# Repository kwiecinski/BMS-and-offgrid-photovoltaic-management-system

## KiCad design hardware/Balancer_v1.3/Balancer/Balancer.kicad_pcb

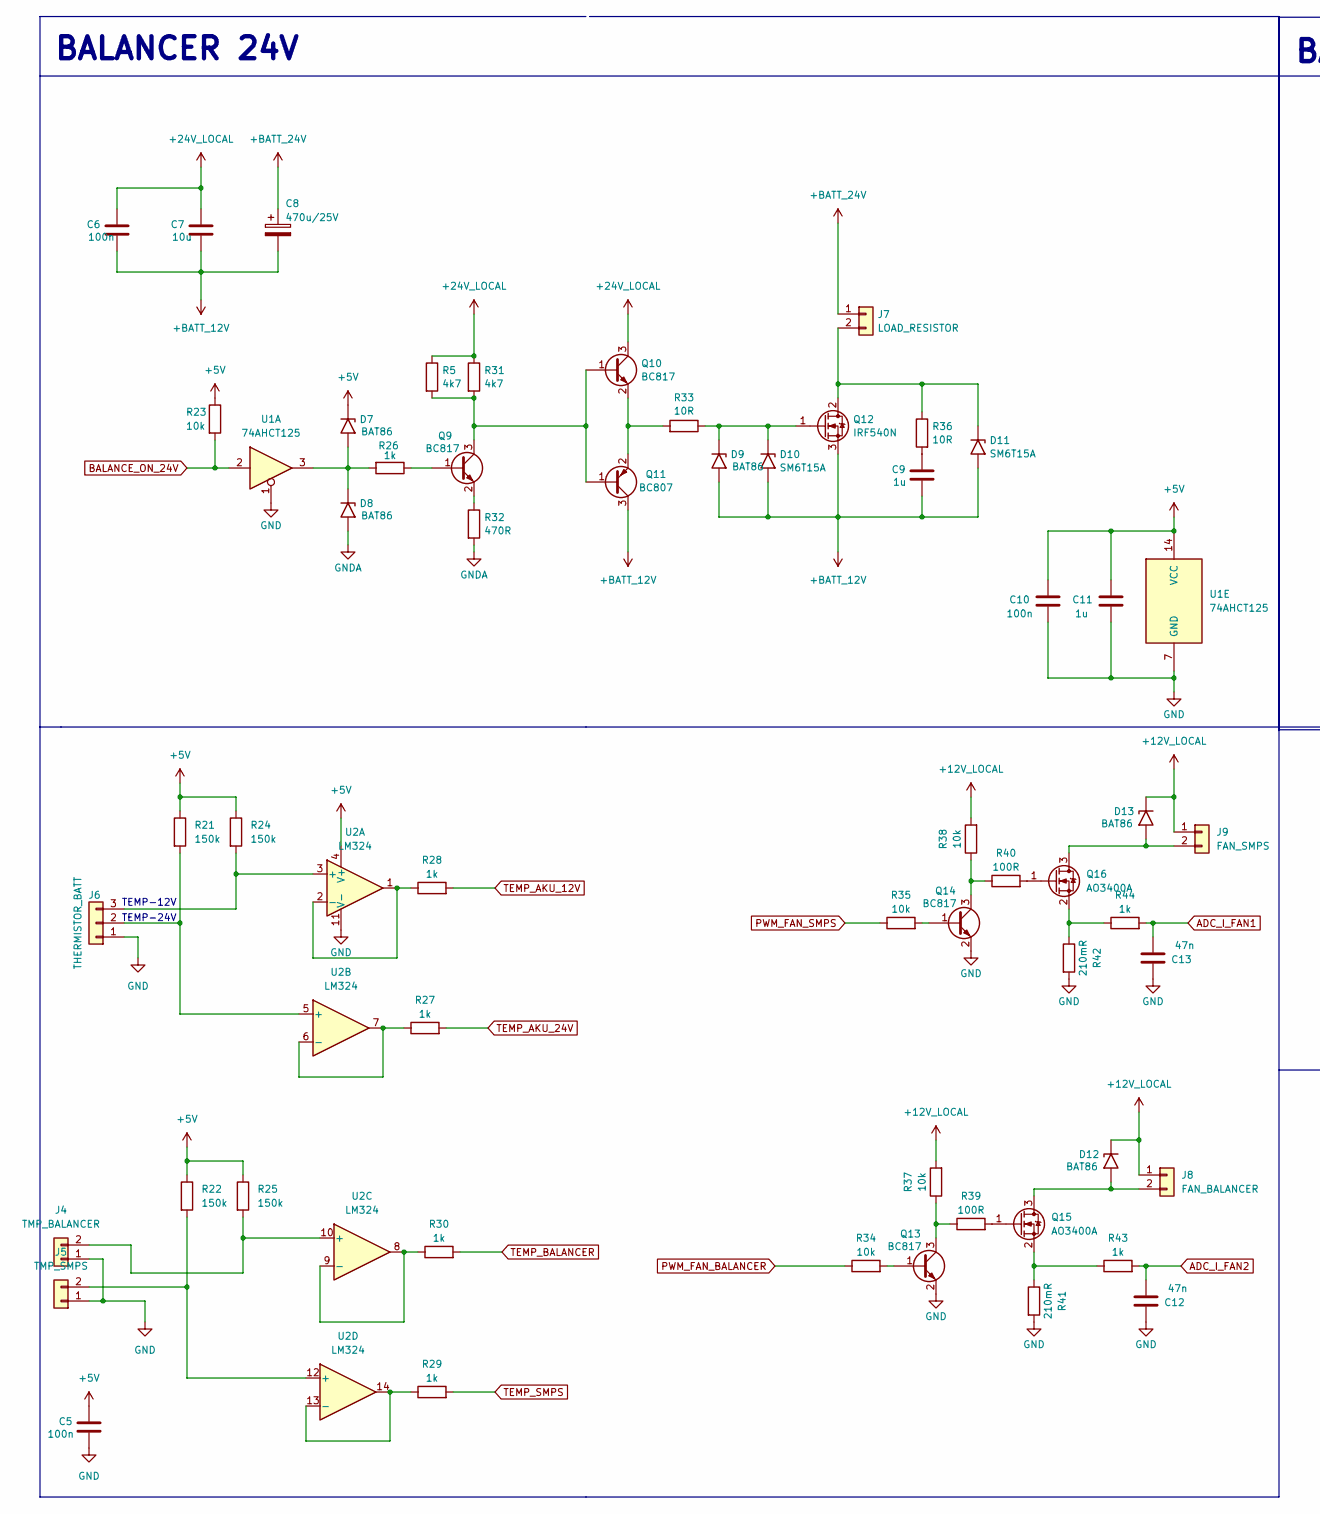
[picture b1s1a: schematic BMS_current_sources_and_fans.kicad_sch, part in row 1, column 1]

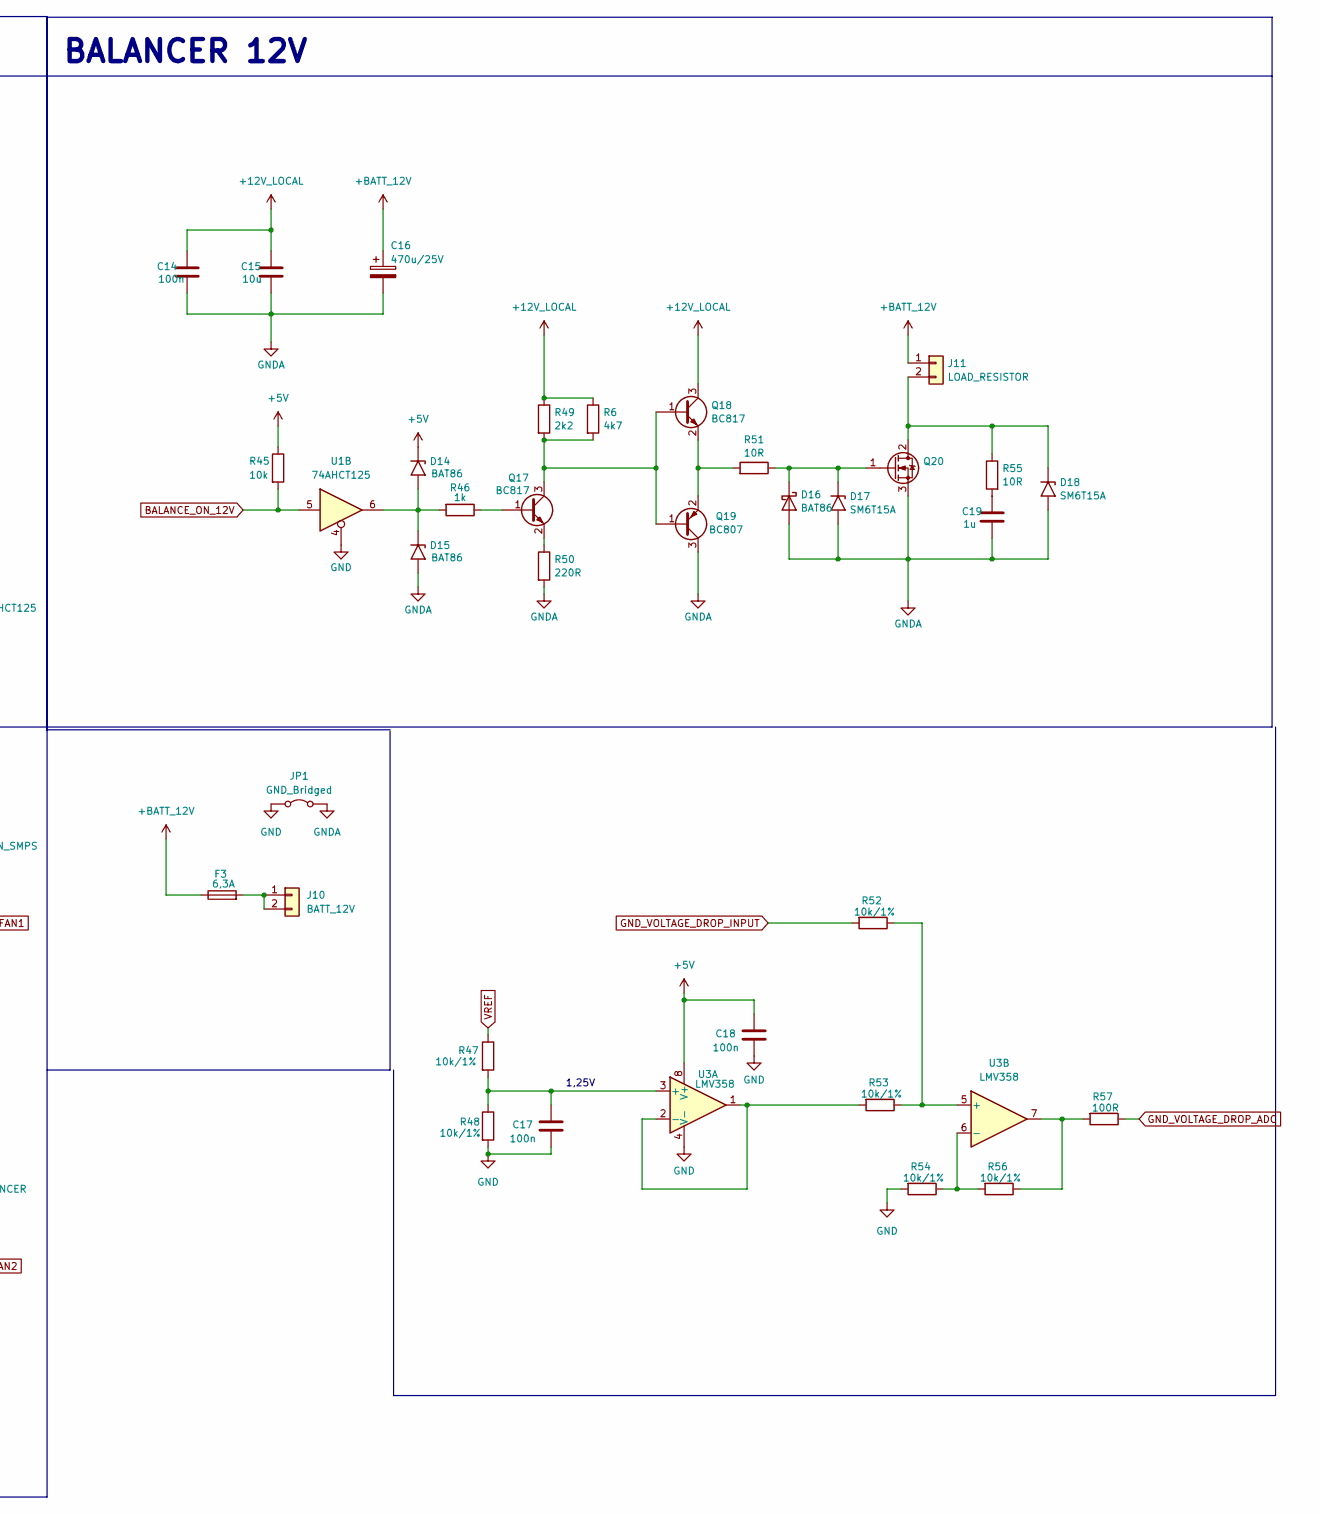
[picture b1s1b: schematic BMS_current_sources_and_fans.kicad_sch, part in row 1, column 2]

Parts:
C5, C6, C10, C14, C17, C18: 100n; C_0805_2012Metric_Pad1.18x1.45mm_HandSolder
C7, C15: 10u; C_0805_2012Metric_Pad1.18x1.45mm_HandSolder
C8, C16: 470u/25V; CP_Radial_D8.0mm_P2.50mm
C9, C19: 1u; C_Disc_D5.0mm_W2.5mm_P2.50mm
C11: 1u; C_0805_2012Metric_Pad1.18x1.45mm_HandSolder
C12, C13: 47n; C_0805_2012Metric_Pad1.18x1.45mm_HandSolder
D7, D8, D9, D12, D13, D14, D15, D16: BAT86; D_MiniMELF
D10, D11, D17, D18: SM6T15A; D_SMB
F3: 6,3A; Fuseholder_Clip-5x20mm_Eaton_1A5601-01_Inline_P20.80x6.76mm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
J4: TMP_BALANCER; JST_EH_B2B-EH-A_1x02_P2.50mm_Vertical
J5: TMP_SMPS; JST_EH_B2B-EH-A_1x02_P2.50mm_Vertical
J6: THERMISTOR_BATT; JST_EH_B3B-EH-A_1x03_P2.50mm_Vertical
J7, J11: LOAD_RESISTOR; Conn_1x2_wire
J8: FAN_BALANCER; JST_EH_B2B-EH-A_1x02_P2.50mm_Vertical
J9: FAN_SMPS; JST_EH_B2B-EH-A_1x02_P2.50mm_Vertical
J10: BATT_12V; Flat-6,3mm-connector-2P
JP1: GND_Bridged; SolderJumper-2_P1.3mm_Bridged2Bar_Pad1.0x1.5mm
Q9, Q10, Q13, Q14, Q17, Q18: BC817; SOT-23
Q11, Q19: BC807; SOT-23
Q12, Q20: IRF540N; TO-220-3_Vertical-little-bigger pads
Q15, Q16: AO3400A; SOT-23
R5, R6, R31: 4k7; R_1206_3216Metric_Pad1.30x1.75mm_HandSolder
R21, R22, R24, R25: 150k; R_0805_2012Metric_Pad1.20x1.40mm_HandSolder
R23, R34, R35, R37, R38, R45: 10k; R_0805_2012Metric_Pad1.20x1.40mm_HandSolder
R26, R27, R28, R29, R30, R43, R44, R46: 1k; R_0805_2012Metric_Pad1.20x1.40mm_HandSolder
R32: 470R; R_0805_2012Metric_Pad1.20x1.40mm_HandSolder
R33, R51: 10R; R_0805_2012Metric_Pad1.20x1.40mm_HandSolder
R36, R55: 10R; R_Axial_DIN0204_L3.6mm_D1.6mm_P7.62mm_Horizontal
R39, R40, R57: 100R; R_0805_2012Metric_Pad1.20x1.40mm_HandSolder
R41, R42: 210mR; R_0805_2012Metric_Pad1.20x1.40mm_HandSolder
R47, R48, R52, R53, R54, R56: 10k/1%; R_0805_2012Metric_Pad1.20x1.40mm_HandSolder
R49: 2k2; R_1206_3216Metric_Pad1.30x1.75mm_HandSolder
R50: 220R; R_0805_2012Metric_Pad1.20x1.40mm_HandSolder
U1: 74AHCT125; SOIC-14_3.9x8.7mm_P1.27mm
U2: LM324; SOIC-14_3.9x8.7mm_P1.27mm
U3: LMV358; SOIC-8_3.9x4.9mm_P1.27mm

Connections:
+5V: C5.1, C10.1, C11.1, C18.1, D7.1 (A1), D14.1 (A1), R21.1, R22.1, R23.1, R24.1, R25.1, R45.1, U1.14 (VCC), U2.4 (V+), U3.8 (V+); also elsewhere on the board
+12V_LOCAL: C14.1, C15.1, D12.1 (A1), D13.1 (A1), J8.1, J9.1, Q18.3 (C), R6.1, R37.2, R38.2, R49.1; also elsewhere on the board
+24V_LOCAL: C6.1, C7.1, Q10.3 (C), R5.1, R31.1; also elsewhere on the board
+BATT_12V: C6.2, C7.2, C8.2, C9.2, C16.1, D9.2 (A2), D10.2 (A2), D11.2 (A2), F3.1, J11.1, Q11.3 (C), Q12.3 (S); also elsewhere on the board
+BATT_24V: C8.1, J7.1; also elsewhere on the board
ADC_I_FAN1: C13.2, R44.2; also elsewhere on the board
ADC_I_FAN2: C12.2, R43.2; also elsewhere on the board
BALANCE_ON_12V: R45.2, U1.5; also elsewhere on the board
BALANCE_ON_24V: R23.2, U1.2; also elsewhere on the board
GND: C5.2, C10.2, C11.2, C12.1, C13.1, C17.2, C18.2, J4.1, J5.1, J6.1, JP1.1 (A), Q13.2 (E), Q14.2 (E), R41.2, R42.2, R48.2, R54.2, U1.1, U1.4, U1.7 (GND), U2.11 (V-), U3.4 (V-); also elsewhere on the board
GNDA: C14.2, C15.2, C16.2, C19.2, D8.2 (A2), D15.2 (A2), D16.2 (A), D17.2 (A2), D18.2 (A2), JP1.2 (B), Q19.3 (C), Q20.3 (S), R32.2, R50.2; also elsewhere on the board
GND_VOLTAGE_DROP_ADC: R57.1; also elsewhere on the board
GND_VOLTAGE_DROP_INPUT: R52.2; also elsewhere on the board
unnamed: C9.1, R36.2
unnamed: C19.1, R55.2
unnamed: D7.2 (A2), D8.1 (A1), R26.2, U1.3
unnamed: D9.1 (A1), D10.1 (A1), Q12.1 (G), R33.1
unnamed: D11.1 (A1), J7.2, Q12.2 (D), R36.1
unnamed: D12.2 (A2), J8.2, Q15.3 (D)
unnamed: D13.2 (A2), J9.2, Q16.3 (D)
unnamed: D14.2 (A2), D15.1 (A1), R46.2, U1.6
unnamed: D16.1 (K), D17.1 (A1), Q20.1 (G), R51.1
unnamed: D18.1 (A1), J11.2, Q20.2 (D), R55.1
unnamed: J4.2, R25.2, U2.10 (+)
unnamed: J5.2, R22.2, U2.12 (+)
unnamed: J6.2, R21.2, U2.5 (+)
unnamed: J6.3, R24.2, U2.3 (+)
unnamed: F3.2, J10.1, J10.2
unnamed: Q9.1 (B), R26.1
unnamed: Q9.2 (E), R32.1
unnamed: Q9.3 (C), Q10.1 (B), Q11.1 (B), R5.2, R31.2
unnamed: Q10.2 (E), Q11.2 (E), R33.2
unnamed: Q13.1 (B), R34.2
unnamed: Q13.3 (C), R37.1, R39.1
unnamed: Q14.1 (B), R35.2
unnamed: Q14.3 (C), R38.1, R40.1
unnamed: Q15.1 (G), R39.2
unnamed: Q15.2 (S), R41.1, R43.1
unnamed: Q16.1 (G), R40.2
unnamed: Q16.2 (S), R42.1, R44.1
unnamed: Q17.1 (B), R46.1
unnamed: Q17.3 (C), Q18.1 (B), Q19.1 (B), R6.2, R49.2
unnamed: Q17.2 (E), R50.1
unnamed: Q18.2 (E), Q19.2 (E), R51.2
unnamed: R56.1, R57.2, U3.7
unnamed: R28.1, U2.1, U2.2 (-)
unnamed: R27.1, U2.6 (-), U2.7
unnamed: R30.1, U2.8, U2.9 (-)
unnamed: R29.1, U2.13 (-), U2.14
unnamed: C17.1, R47.2, R48.1, U3.3 (+)
unnamed: R53.2, U3.1, U3.2 (-)
unnamed: R52.1, R53.1, U3.5 (+)
unnamed: R54.1, R56.2, U3.6 (-)
PWM_FAN_BALANCER: R34.1; also elsewhere on the board
PWM_FAN_SMPS: R35.1; also elsewhere on the board
TEMP_AKU_12V: R28.2; also elsewhere on the board
TEMP_AKU_24V: R27.2; also elsewhere on the board
TEMP_BALANCER: R30.2; also elsewhere on the board
TEMP_SMPS: R29.2; also elsewhere on the board
VREF: R47.1; also elsewhere on the board

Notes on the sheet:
1,25V
BALANCER 12V
TEMP-12V
TEMP-24V
BALANCER 24V

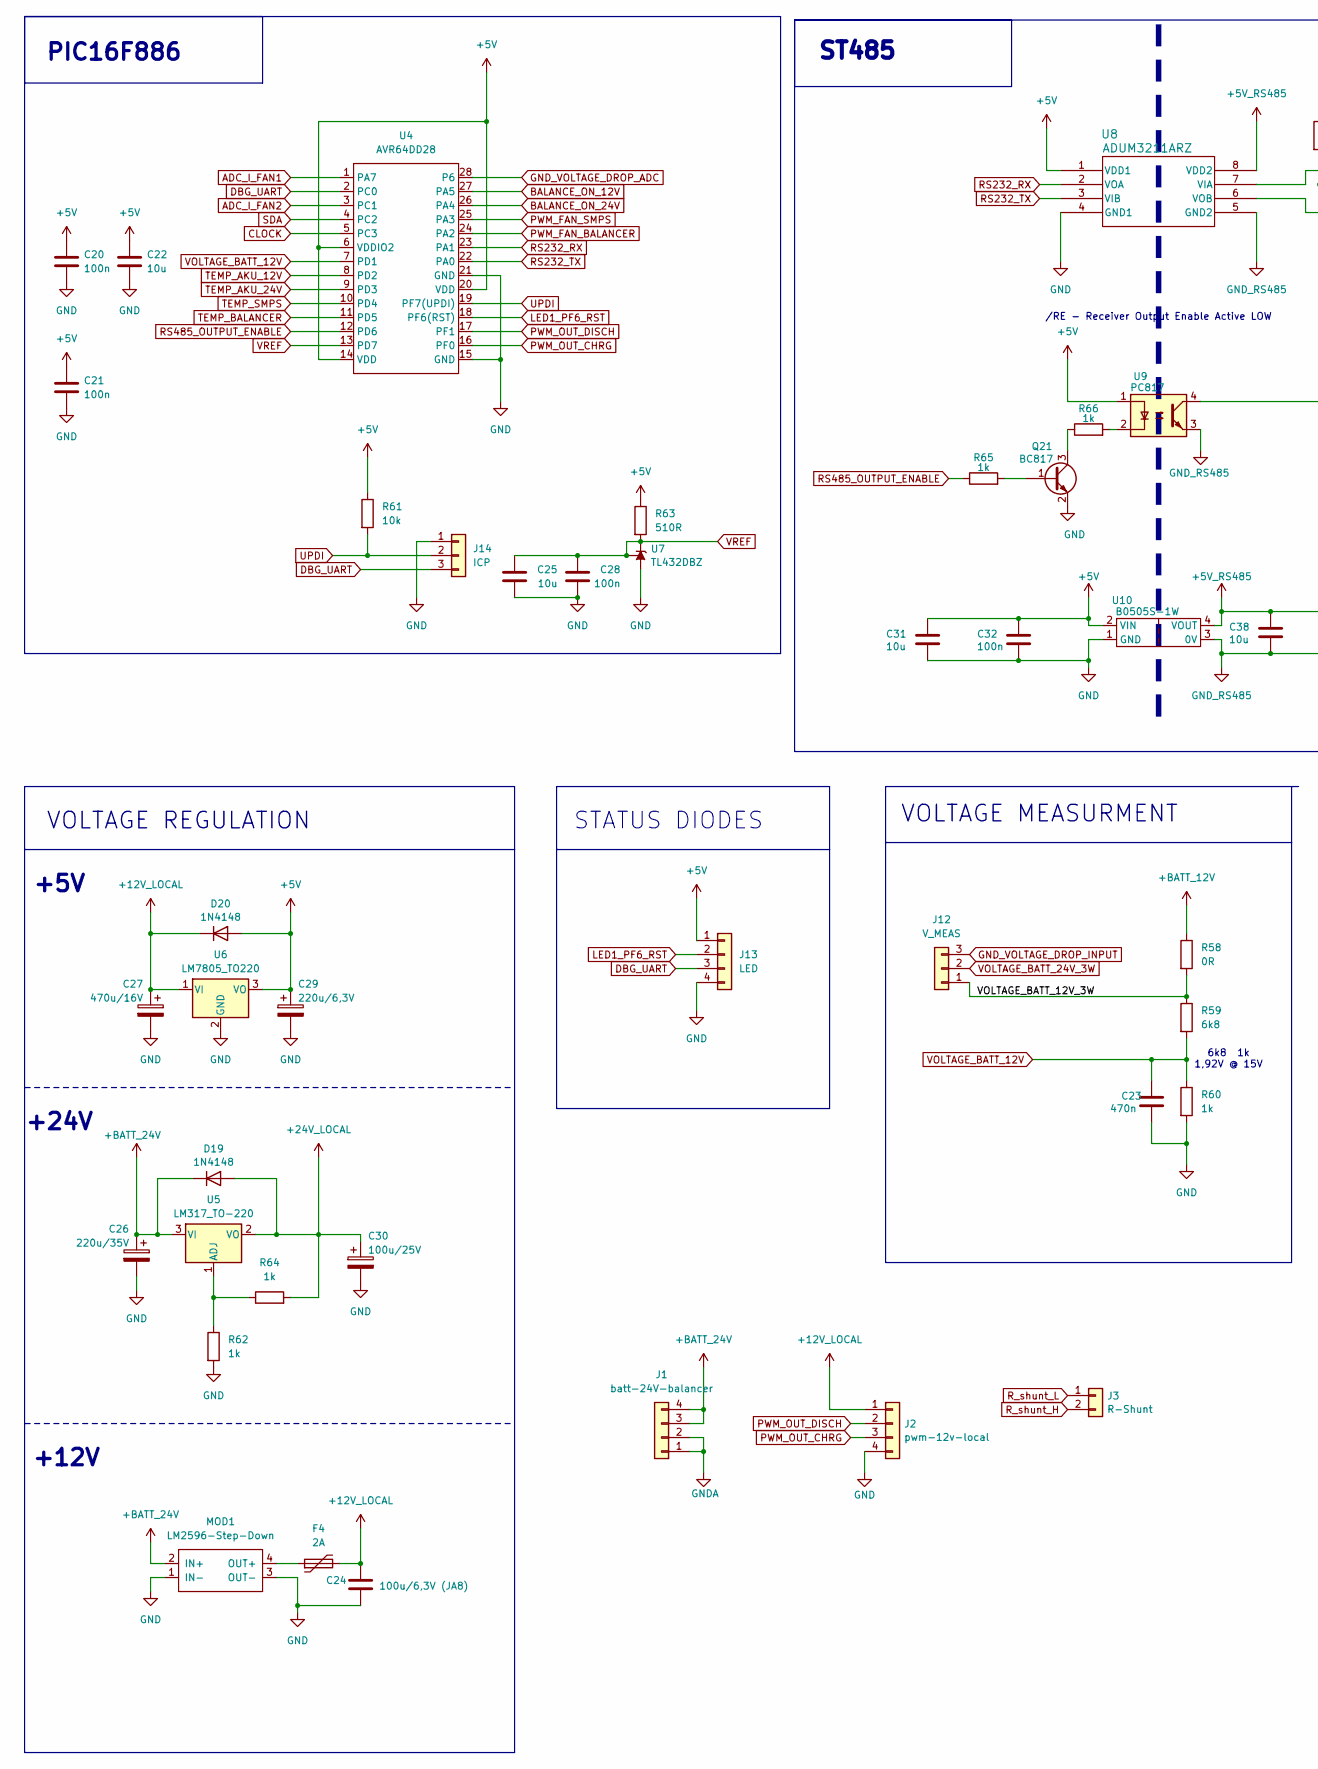
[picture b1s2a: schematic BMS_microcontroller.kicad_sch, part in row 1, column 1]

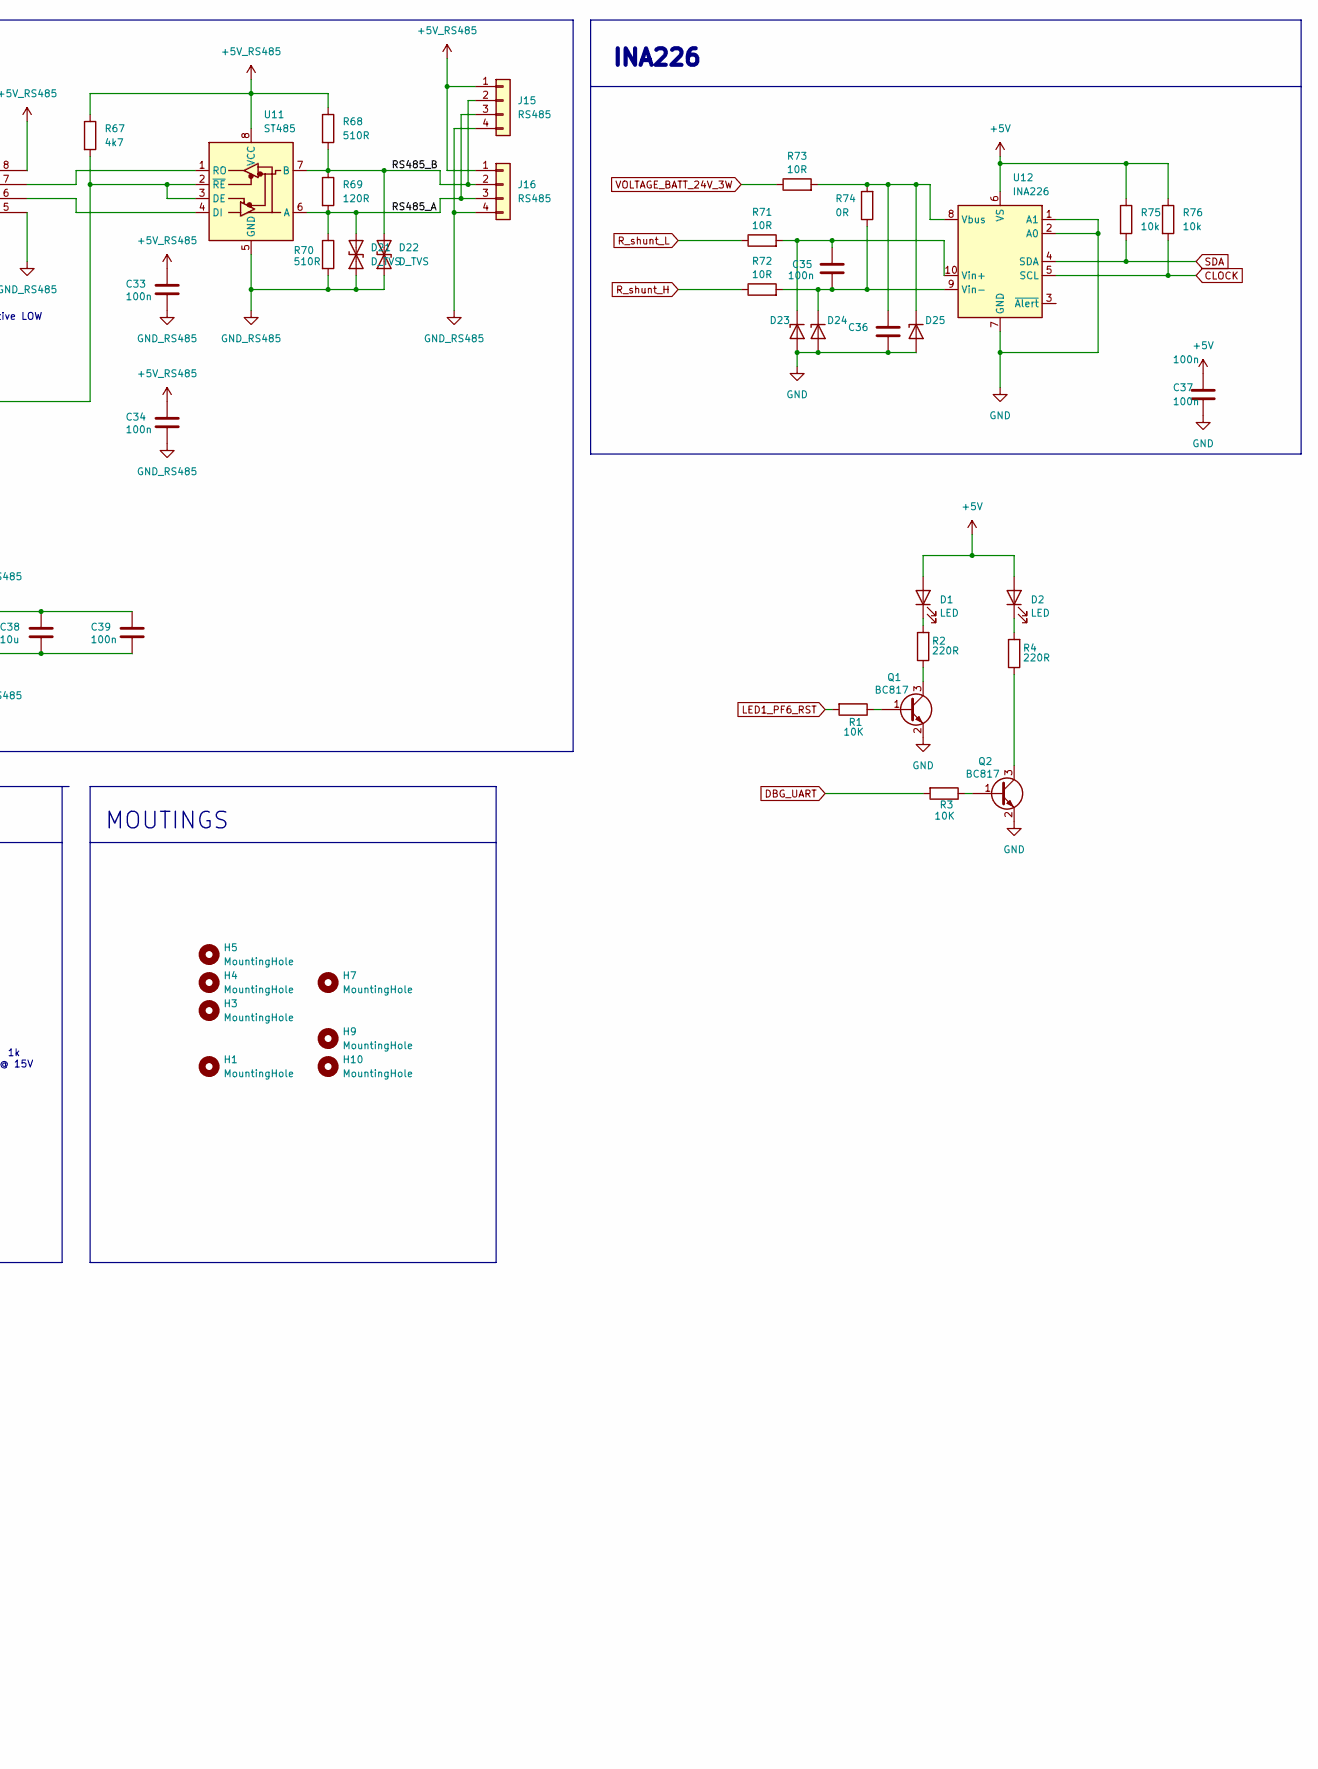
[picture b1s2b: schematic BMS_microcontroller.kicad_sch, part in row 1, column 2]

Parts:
C20, C21, C28, C32, C33, C34, C39: 100n; C_0805_2012Metric_Pad1.18x1.45mm_HandSolder
C22, C25: 10u; C_0805_2012Metric_Pad1.18x1.45mm_HandSolder
C23: 470n; C_0805_2012Metric_Pad1.18x1.45mm_HandSolder
C24: 100u/6,3V (JA8); CP_EIA-3528-21_Kemet-B
C26: 220u/35V; CP_Radial_D8.0mm_P2.50mm
C27: 470u/16V; CP_Radial_D8.0mm_P2.50mm
C29: 220u/6,3V; CP_Radial_D8.0mm_P2.50mm
C30: 100u/25V; CP_Radial_D8.0mm_P2.50mm
C31, C38: 10u; C_1206_3216Metric
C35, C36, C37: 100n; R_0805_2012Metric_Pad1.20x1.40mm_HandSolder
D1, D2: LED; LED_D5.0mm
D19, D20: 1N4148; D_MiniMELF
D21, D22: D_TVS; Nexperia_CFP3_SOD-123W
D23, D24, D25: PTVS5V0Z1USK; D_SOD-123
F4: 2A; Fuse_2920_7451Metric_Pad2.10x5.45mm_HandSolder
H1, H3, H4, H5, H7, H9, H10: MountingHole; Mount-Hole-3mm
J1: batt-24V-balancer; PinSocket_1x04_P2.54mm_Vertical
J2: pwm-12v-local; PinSocket_1x04_P2.54mm_Vertical
J3: R-Shunt; PinHeader_1x02_P2.54mm_Vertical
J12: V_MEAS; JST_XA_1x03_P2.54mm_Vertical
J13: LED; JST_XH_B4B-XH-A_1x04_P2.50mm_Vertical
J14: ICP; JST_XA_1x03_P2.54mm_Vertical
J15, J16: RS485; Conn-01x04-N25-W4P
MOD1: LM2596-Step-Down; LM2596-Step-Down-Conv
Q1, Q2, Q21: BC817; SOT-23
R1, R3: 10K; R_0805_2012Metric_Pad1.20x1.40mm_HandSolder
R2, R4: 220R; R_0805_2012Metric_Pad1.20x1.40mm_HandSolder
R58, R74: 0R; R_0805_2012Metric_Pad1.20x1.40mm_HandSolder
R59: 6k8; R_0805_2012Metric_Pad1.20x1.40mm_HandSolder
R60, R62, R64, R65, R66: 1k; R_0805_2012Metric_Pad1.20x1.40mm_HandSolder
R61, R75, R76: 10k; R_0805_2012Metric_Pad1.20x1.40mm_HandSolder
R63, R68, R70: 510R; R_0805_2012Metric_Pad1.20x1.40mm_HandSolder
R67: 4k7; R_0805_2012Metric_Pad1.20x1.40mm_HandSolder
R69: 120R; R_0805_2012Metric_Pad1.20x1.40mm_HandSolder
R71, R72, R73: 10R; R_0805_2012Metric_Pad1.20x1.40mm_HandSolder
U4: AVR64DD28; SOIC-28W_7.5x17.9mm_P1.27mm
U5: LM317_TO-220; TO-220-3_Vertical-little-bigger pads
U6: LM7805_TO220; TO-220-3_Vertical-little-bigger pads
U7: TL432DBZ; SOT-23
U8: ADUM3211ARZ; SO-8_3.9x4.9mm_P1.27mm
U9: PC817; DIP-4_W7.62mm
U10: B0505S-1W; B0505S
U11: ST485; SOIC-8_3.9x4.9mm_P1.27mm
U12: INA226; VSSOP-10_3x3mm_P0.5mm

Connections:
+5V: C20.1, C21.1, C22.1, C29.1, C31.1, C32.1, C37.1, D1.2 (A), D2.2 (A), D20.2 (A), J13.1, R61.1, R63.1, R75.1, R76.1, U4.6 (VDDIO2), U4.14 (VDD), U4.20 (VDD), U6.3 (VO), U8.1 (VDD1), U9.1, U10.2 (VIN), U12.6 (VS); also elsewhere on the board
+5V_RS485: C33.1, C34.1, C38.1, C39.1, J15.1, J16.1, R67.1, R68.1, U8.8 (VDD2), U10.4 (VOUT), U11.8 (VCC)
+12V_LOCAL: C24.1, C27.1, D20.1 (K), F4.2, J2.1, U6.1 (VI); also elsewhere on the board
+24V_LOCAL: C30.1, D19.2 (A), R64.2, U5.2 (VO); also elsewhere on the board
+BATT_12V: R58.1; also elsewhere on the board
+BATT_24V: C26.1, D19.1 (K), J1.3, J1.4, MOD1.2 (IN+), U5.3 (VI); also elsewhere on the board
/BMS_microcontroller/RS485_A: D21.2 (A2), J15.3, J16.3, R69.2, R70.1, U11.6 (A)
/BMS_microcontroller/RS485_B: D22.2 (A2), J15.2, J16.2, R68.2, R69.1, U11.7 (B)
/BMS_microcontroller/VOLTAGE_BATT_12V_3W: J12.1, R58.2, R59.1
ADC_I_FAN1: U4.1 (PA7); also elsewhere on the board
ADC_I_FAN2: U4.3 (PC1); also elsewhere on the board
BALANCE_ON_12V: U4.27 (PA5); also elsewhere on the board
BALANCE_ON_24V: U4.26 (PA4); also elsewhere on the board
CLOCK: R76.2, U4.5 (PC3), U12.5 (SCL)
DBG_UART: J13.3, J14.3, R3.2, U4.2 (PC0)
GND: C20.2, C21.2, C22.2, C23.2, C24.2, C25.2, C26.2, C27.2, C28.2, C29.2, C30.2, C31.2, C32.2, C36.2, C37.2, D23.2 (A), D24.2 (A), D25.2 (A), J2.4, J13.4, J14.1, MOD1.1 (IN-), MOD1.3 (OUT-), Q1.2 (E), Q2.2 (E), Q21.2 (E), R60.2, R62.2, U4.15 (GND), U4.21 (GND), U6.2 (GND), U7.3 (A), U8.4 (GND1), U10.1 (GND), U12.1 (A1), U12.2 (A0), U12.7 (GND); also elsewhere on the board
GNDA: J1.1, J1.2; also elsewhere on the board
GND_RS485: C33.2, C34.2, C38.2, C39.2, D21.1 (A1), D22.1 (A1), J15.4, J16.4, R70.2, U8.5 (GND2), U9.3, U10.3 (0V), U11.5 (GND)
GND_VOLTAGE_DROP_ADC: U4.28 (P6); also elsewhere on the board
GND_VOLTAGE_DROP_INPUT: J12.3; also elsewhere on the board
LED1_PF6_RST: J13.2, R1.2, U4.18 (PF6(RST))
unnamed: D1.1 (K), R2.2
unnamed: D2.1 (K), R4.2
unnamed: C35.1, D23.1 (K), R71.2, U12.10 (Vin+)
unnamed: C35.2, D24.1 (K), R72.2, R74.1, U12.9 (Vin-)
unnamed: C36.1, D25.1 (K), R73.2, R74.2, U12.8 (Vbus)
unnamed: F4.1, MOD1.4 (OUT+)
unnamed: Q1.1 (B), R1.1
unnamed: Q1.3 (C), R2.1
unnamed: Q2.1 (B), R3.1
unnamed: Q2.3 (C), R4.1
unnamed: Q21.1 (B), R65.2
unnamed: Q21.3 (C), R66.1
unnamed: R66.2, U9.2
unnamed: R62.1, R64.1, U5.1 (ADJ)
unnamed: R67.2, U9.4, U11.2 (~RE), U11.3 (DE)
unnamed: U8.6 (VOB), U11.4 (DI)
unnamed: U8.7 (VIA), U11.1 (RO)
PWM_FAN_BALANCER: U4.24 (PA2); also elsewhere on the board
PWM_FAN_SMPS: U4.25 (PA3); also elsewhere on the board
PWM_OUT_CHRG: J2.3, U4.16 (PF0)
PWM_OUT_DISCH: J2.2, U4.17 (PF1)
RS232_RX: U4.23 (PA1), U8.2 (VOA)
RS232_TX: U4.22 (PA0), U8.3 (VIB)
RS485_OUTPUT_ENABLE: R65.1, U4.12 (PD6)
R_shunt_H: J3.2, R72.1
R_shunt_L: J3.1, R71.1
SDA: R75.2, U4.4 (PC2), U12.4 (SDA)
TEMP_AKU_12V: U4.8 (PD2); also elsewhere on the board
TEMP_AKU_24V: U4.9 (PD3); also elsewhere on the board
TEMP_BALANCER: U4.11 (PD5); also elsewhere on the board
TEMP_SMPS: U4.10 (PD4); also elsewhere on the board
UPDI: J14.2, R61.2, U4.19 (PF7(UPDI))
VOLTAGE_BATT_12V: C23.1, R59.2, R60.1, U4.7 (PD1)
VOLTAGE_BATT_24V_3W: J12.2, R73.1
VREF: C25.1, C28.1, R63.2, U4.13 (PD7), U7.1 (REF), U7.2 (K); also elsewhere on the board

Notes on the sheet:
+24V
6k8 1k 1,92V @ 15V
INA226
+12V
+5V
PIC16F886
MOUTINGS
VOLTAGE MEASURMENT
ST485
VOLTAGE REGULATION
/RE - Receiver Output Enable Active LOW
STATUS DIODES

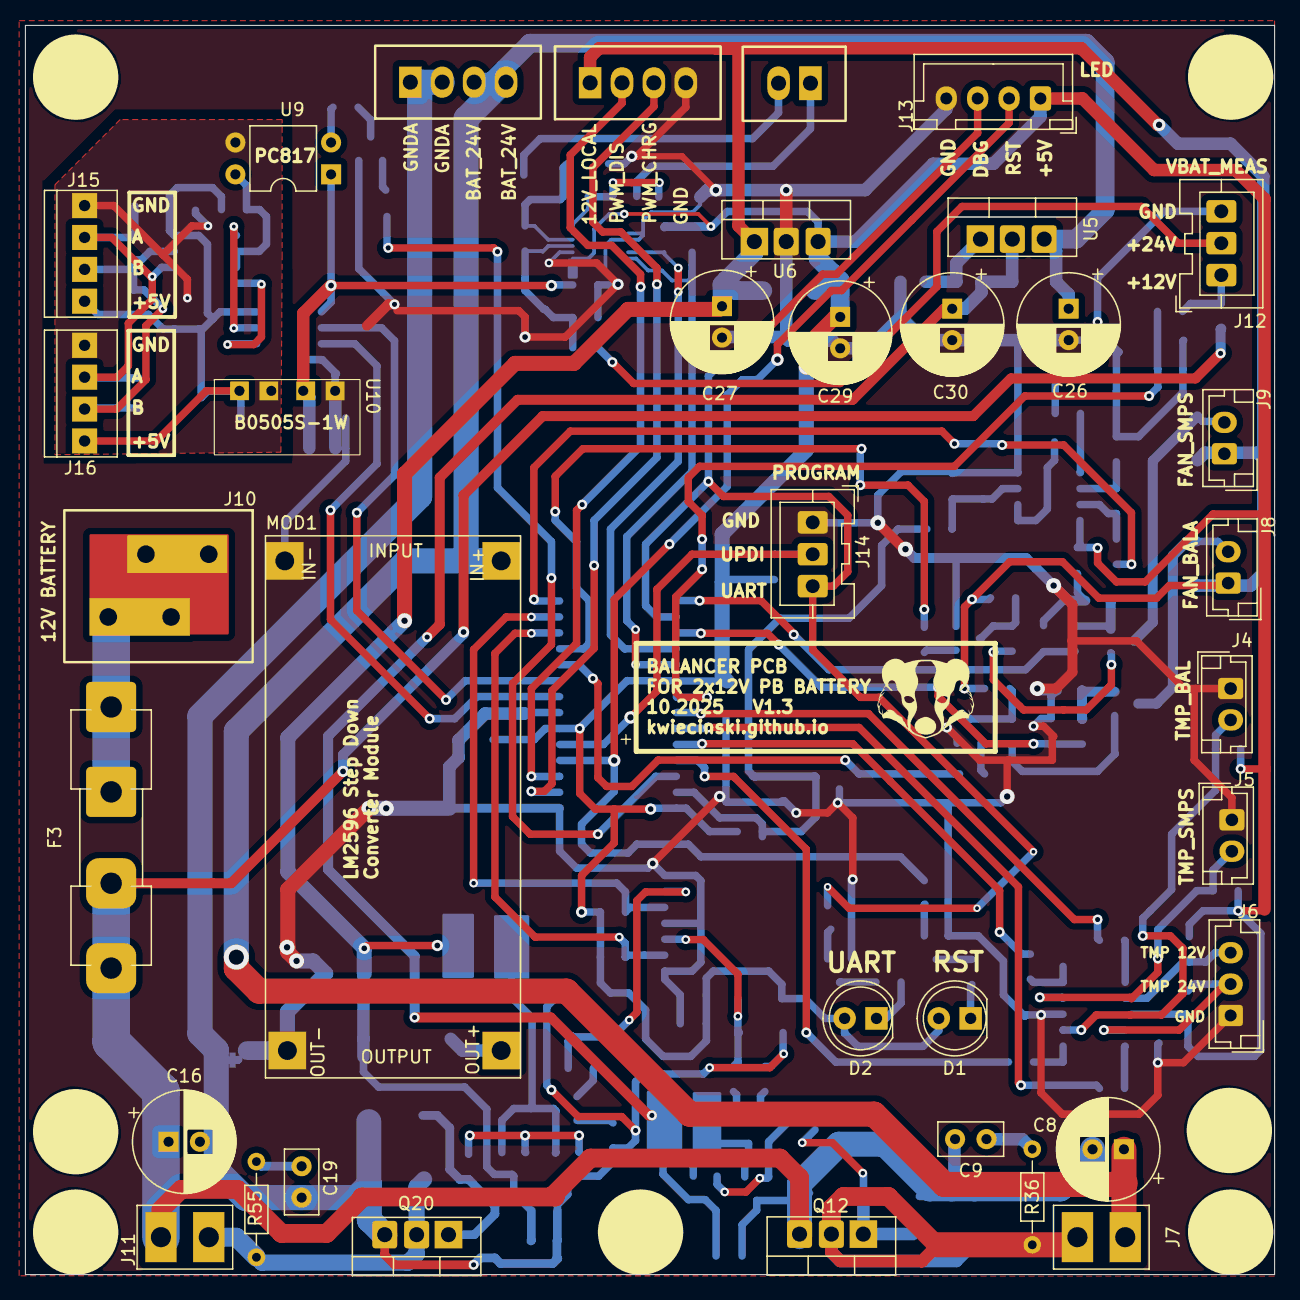
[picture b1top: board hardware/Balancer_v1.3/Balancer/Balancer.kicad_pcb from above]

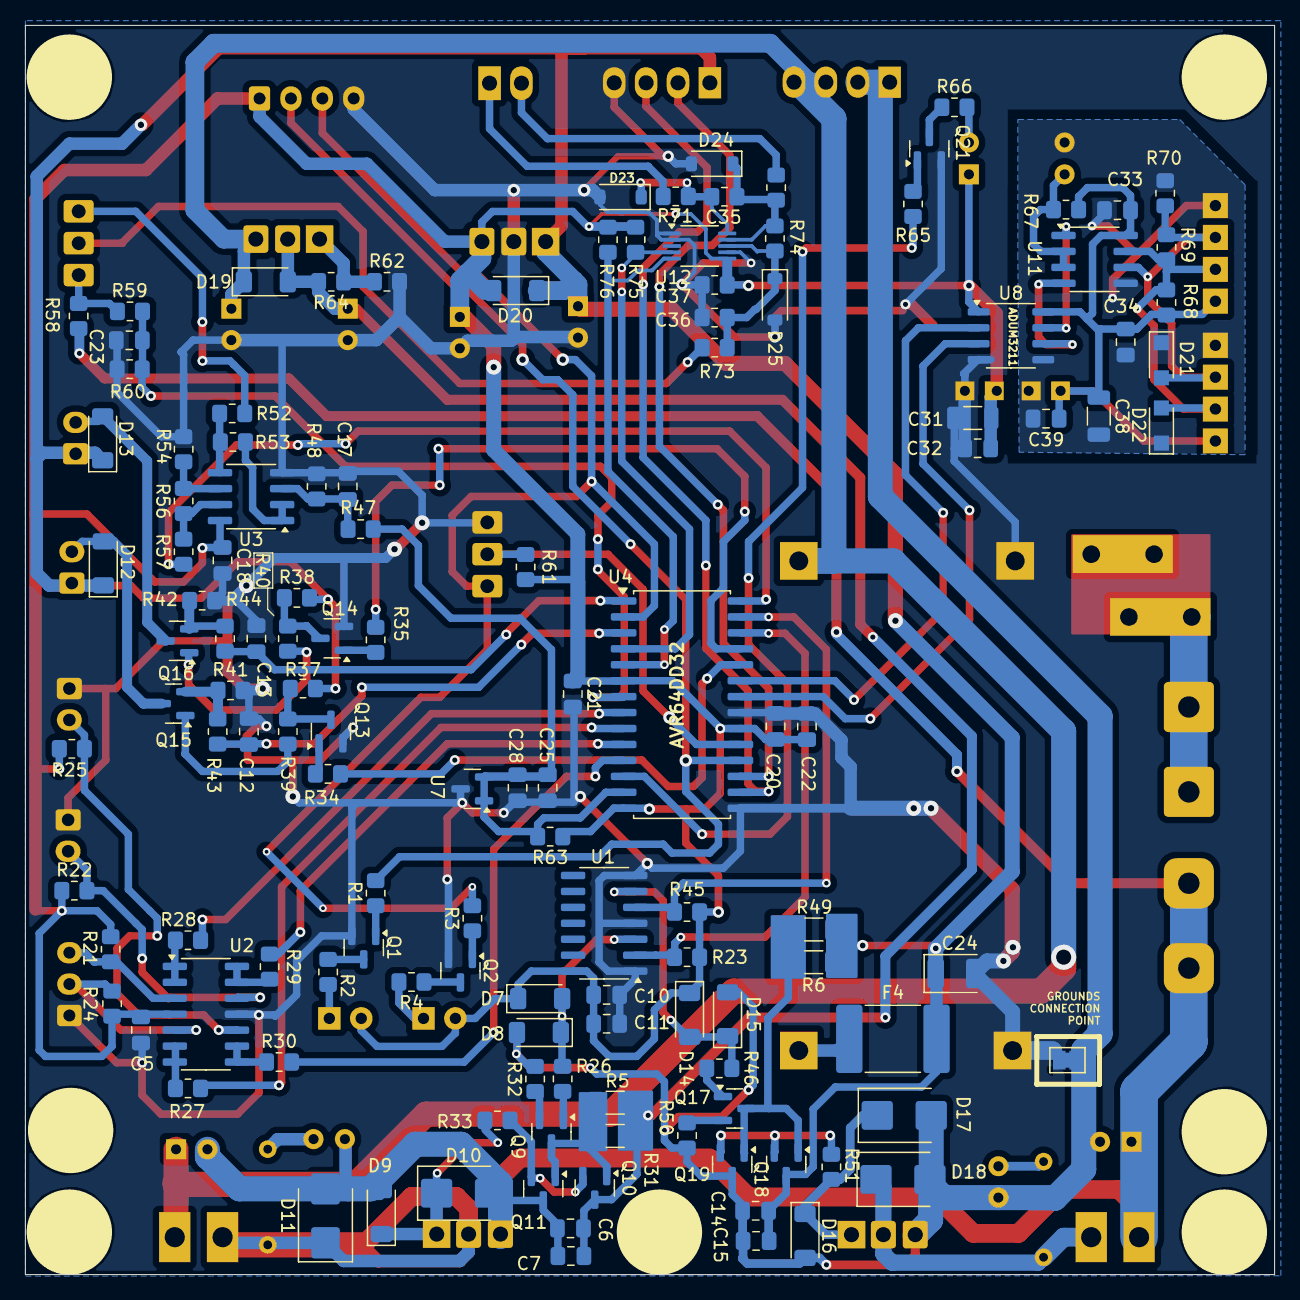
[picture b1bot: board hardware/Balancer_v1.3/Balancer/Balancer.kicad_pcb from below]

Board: 2 copper layers, 99.5 x 99.5 mm, 172 parts (129 on the bottom side), 96 nets.
